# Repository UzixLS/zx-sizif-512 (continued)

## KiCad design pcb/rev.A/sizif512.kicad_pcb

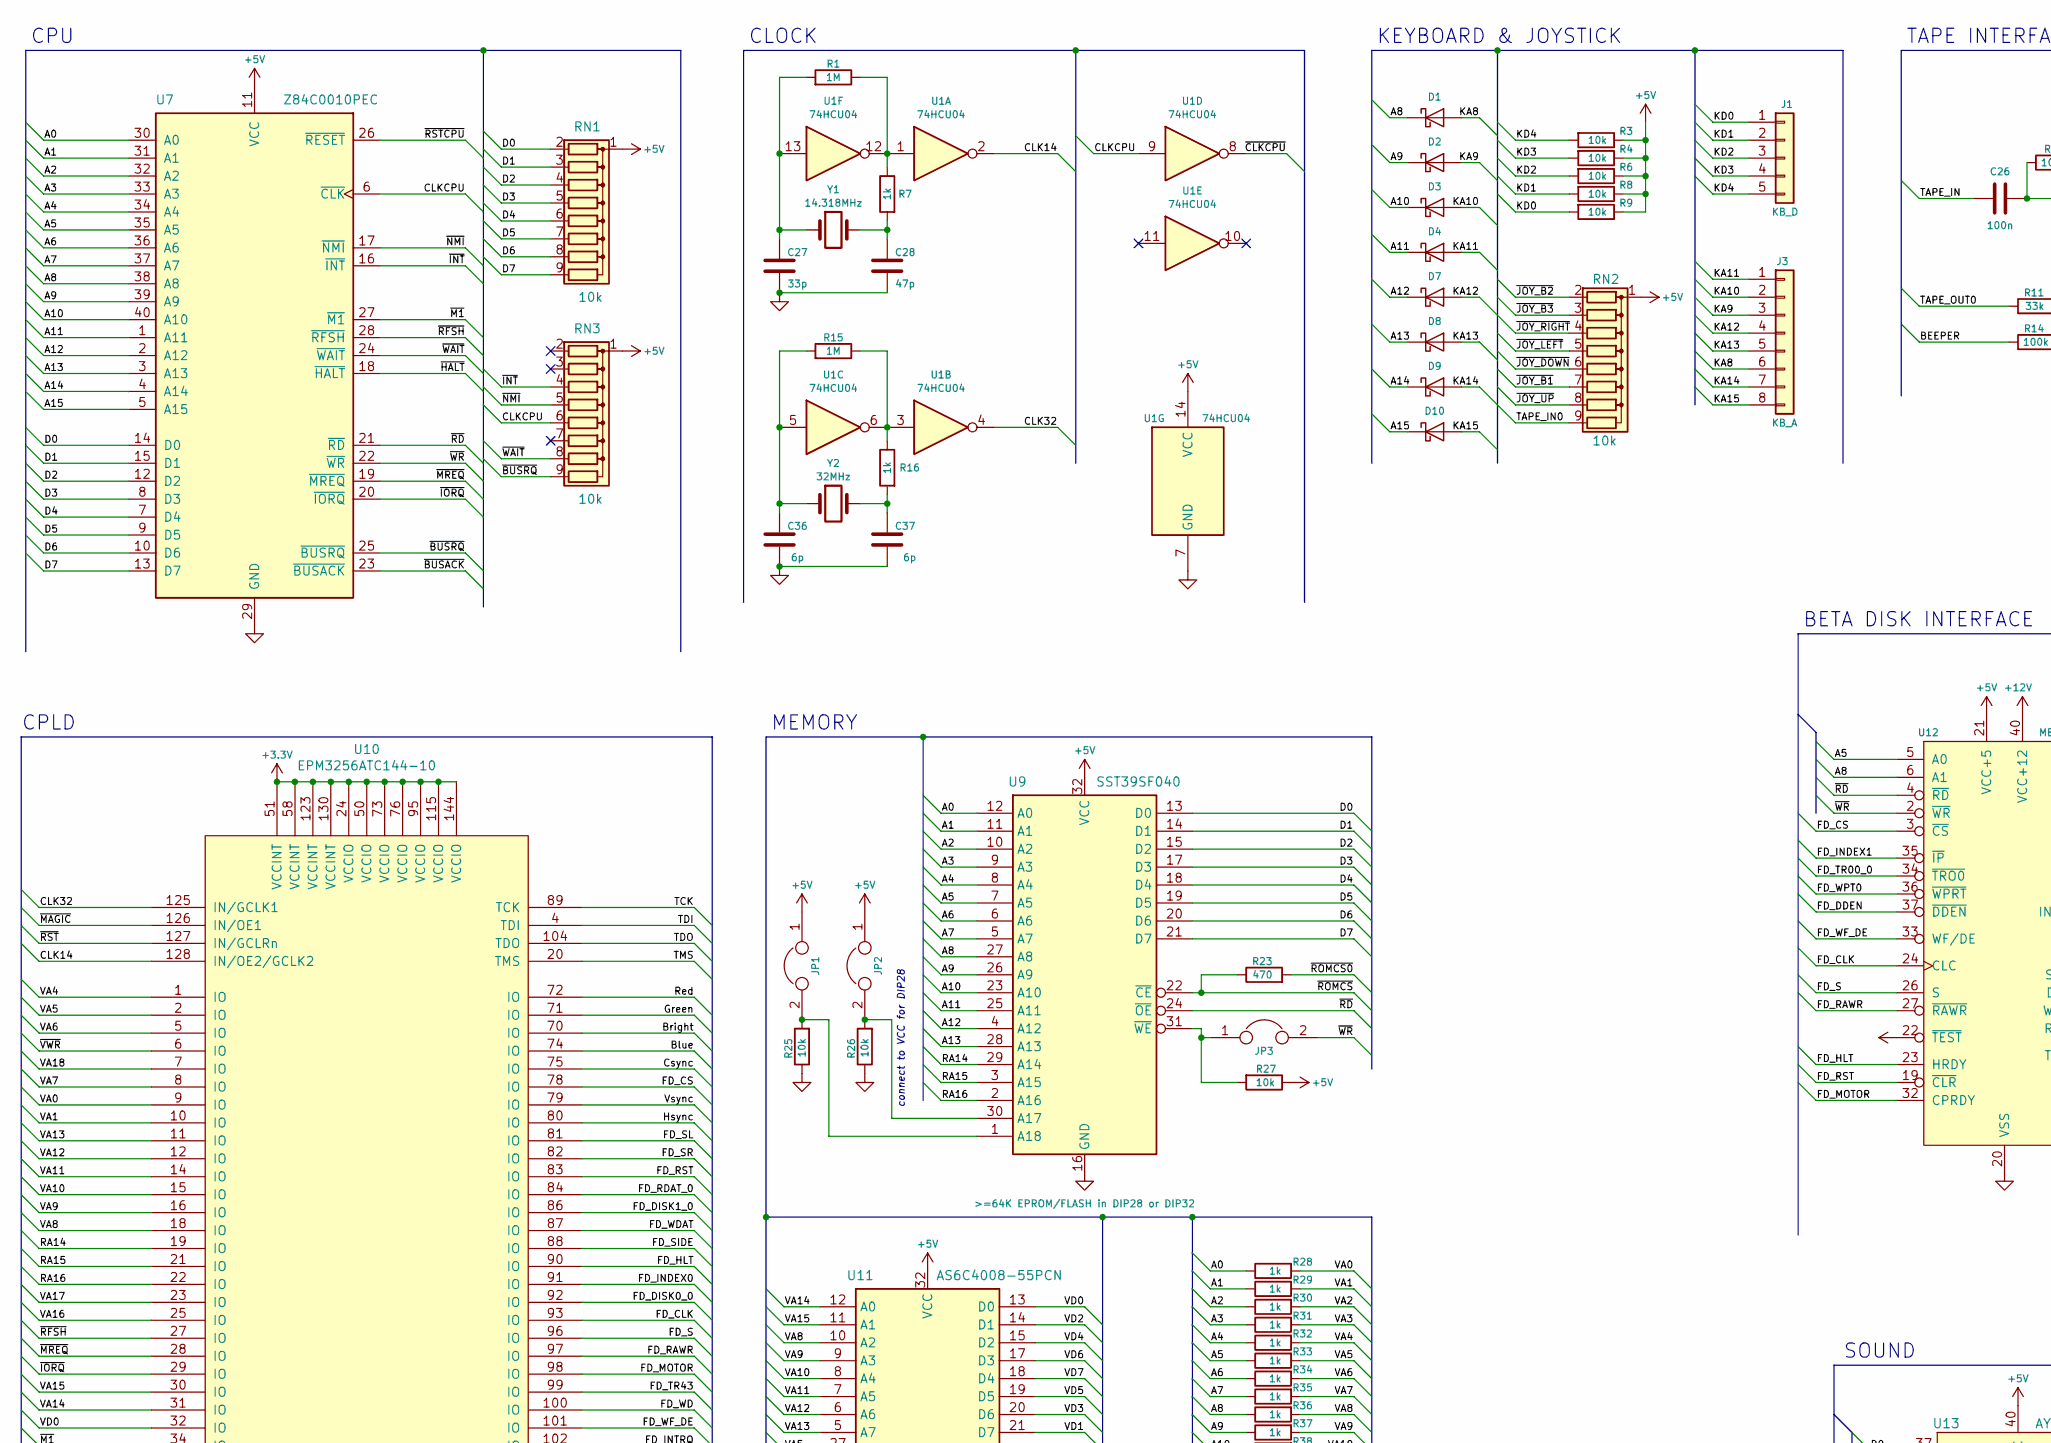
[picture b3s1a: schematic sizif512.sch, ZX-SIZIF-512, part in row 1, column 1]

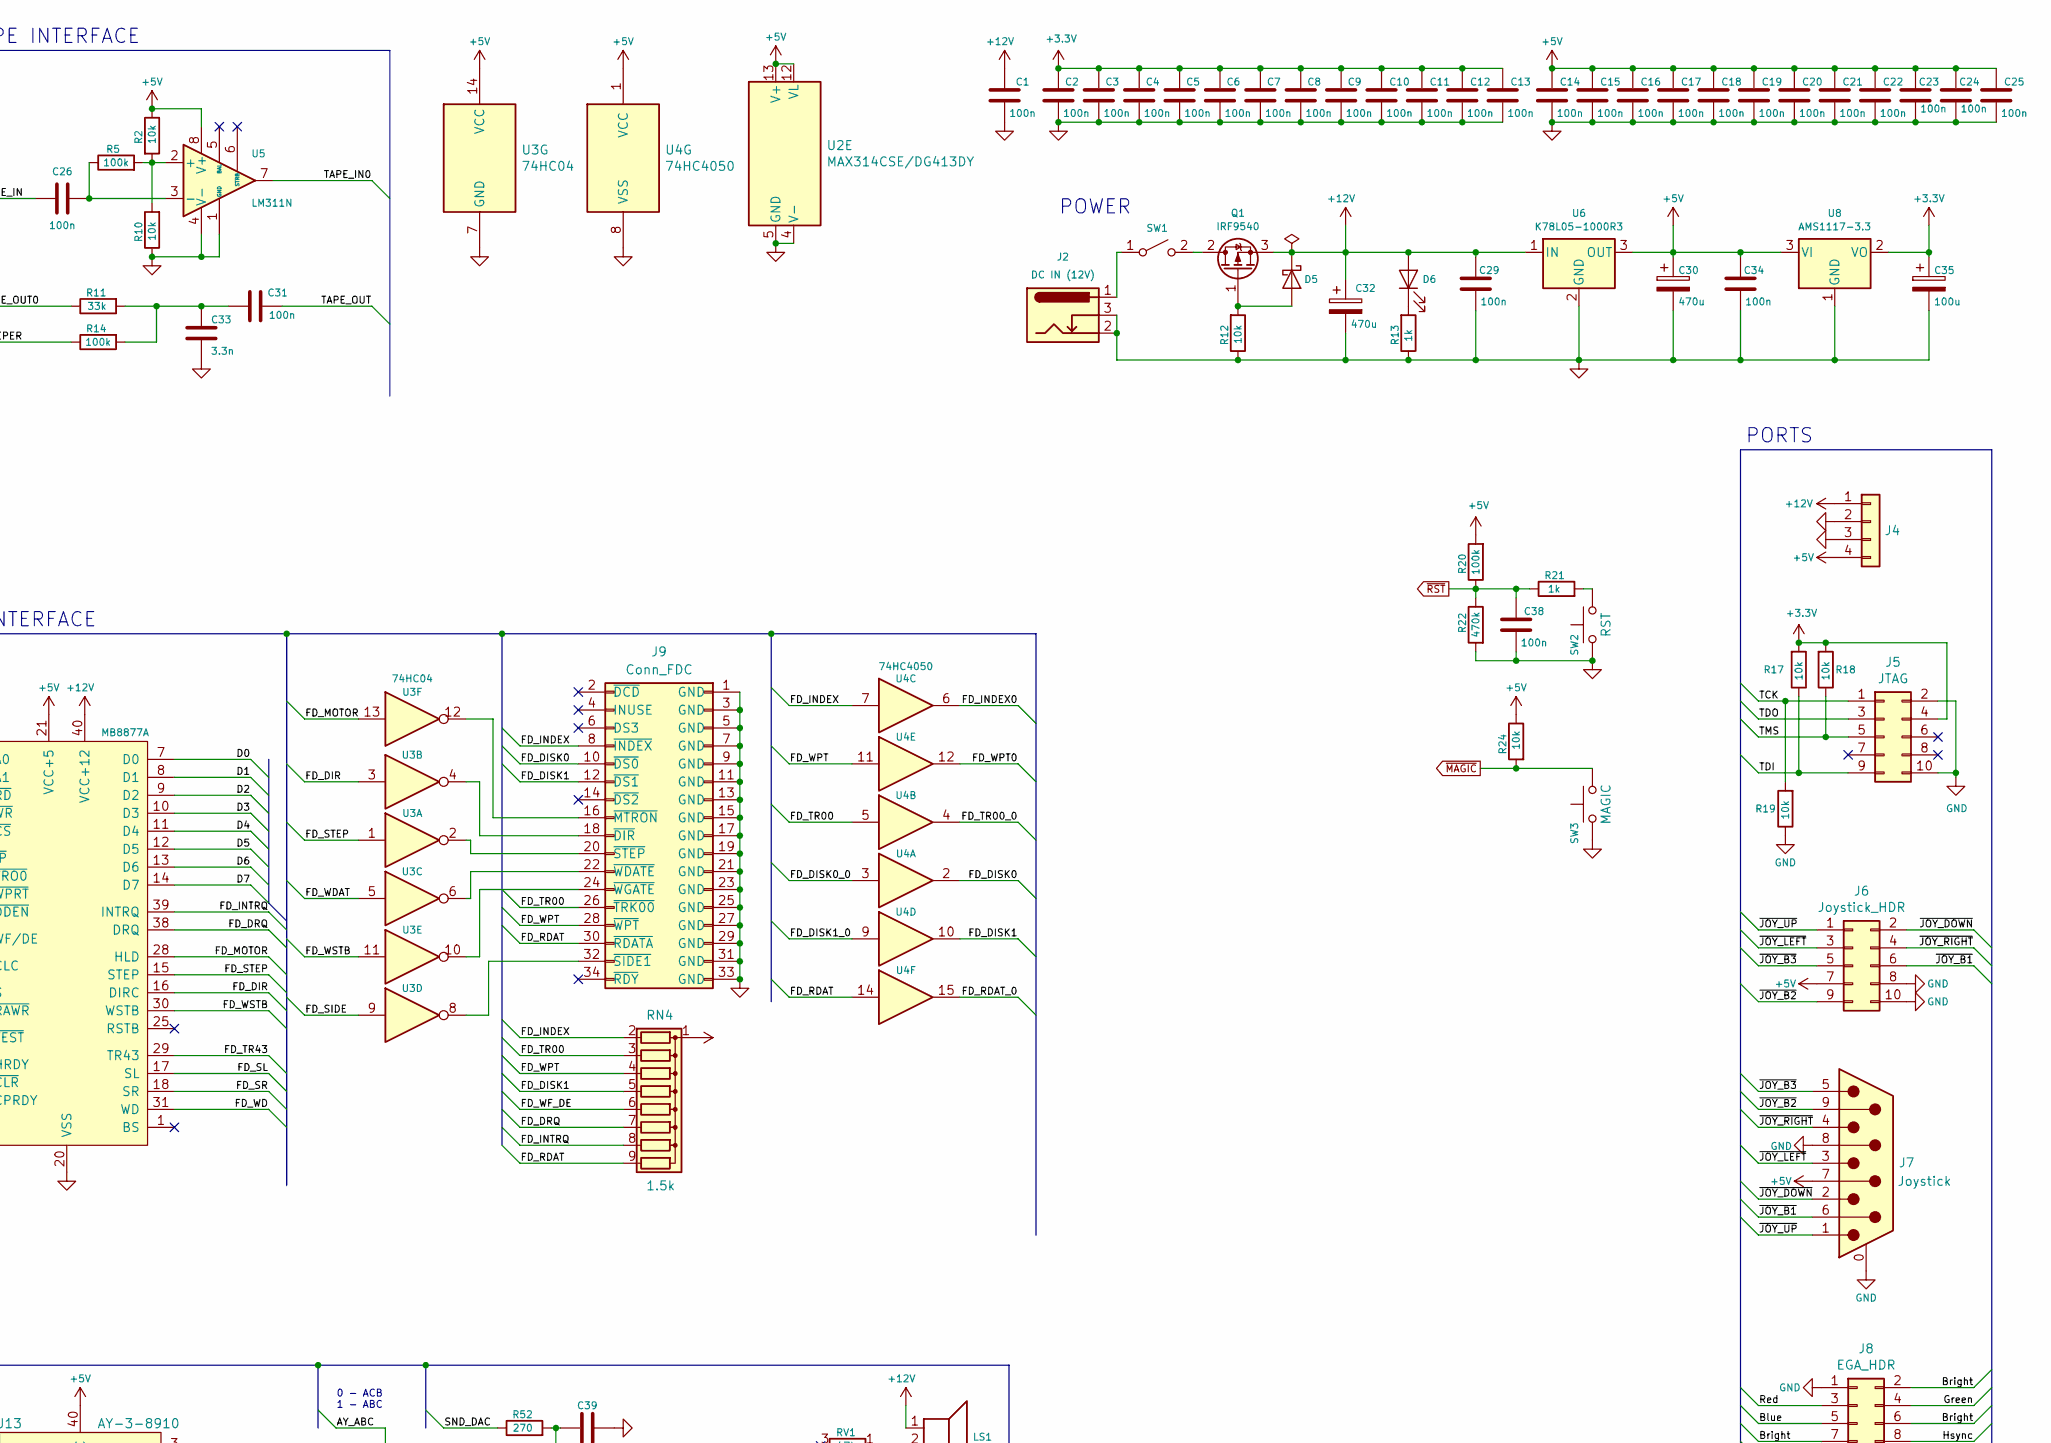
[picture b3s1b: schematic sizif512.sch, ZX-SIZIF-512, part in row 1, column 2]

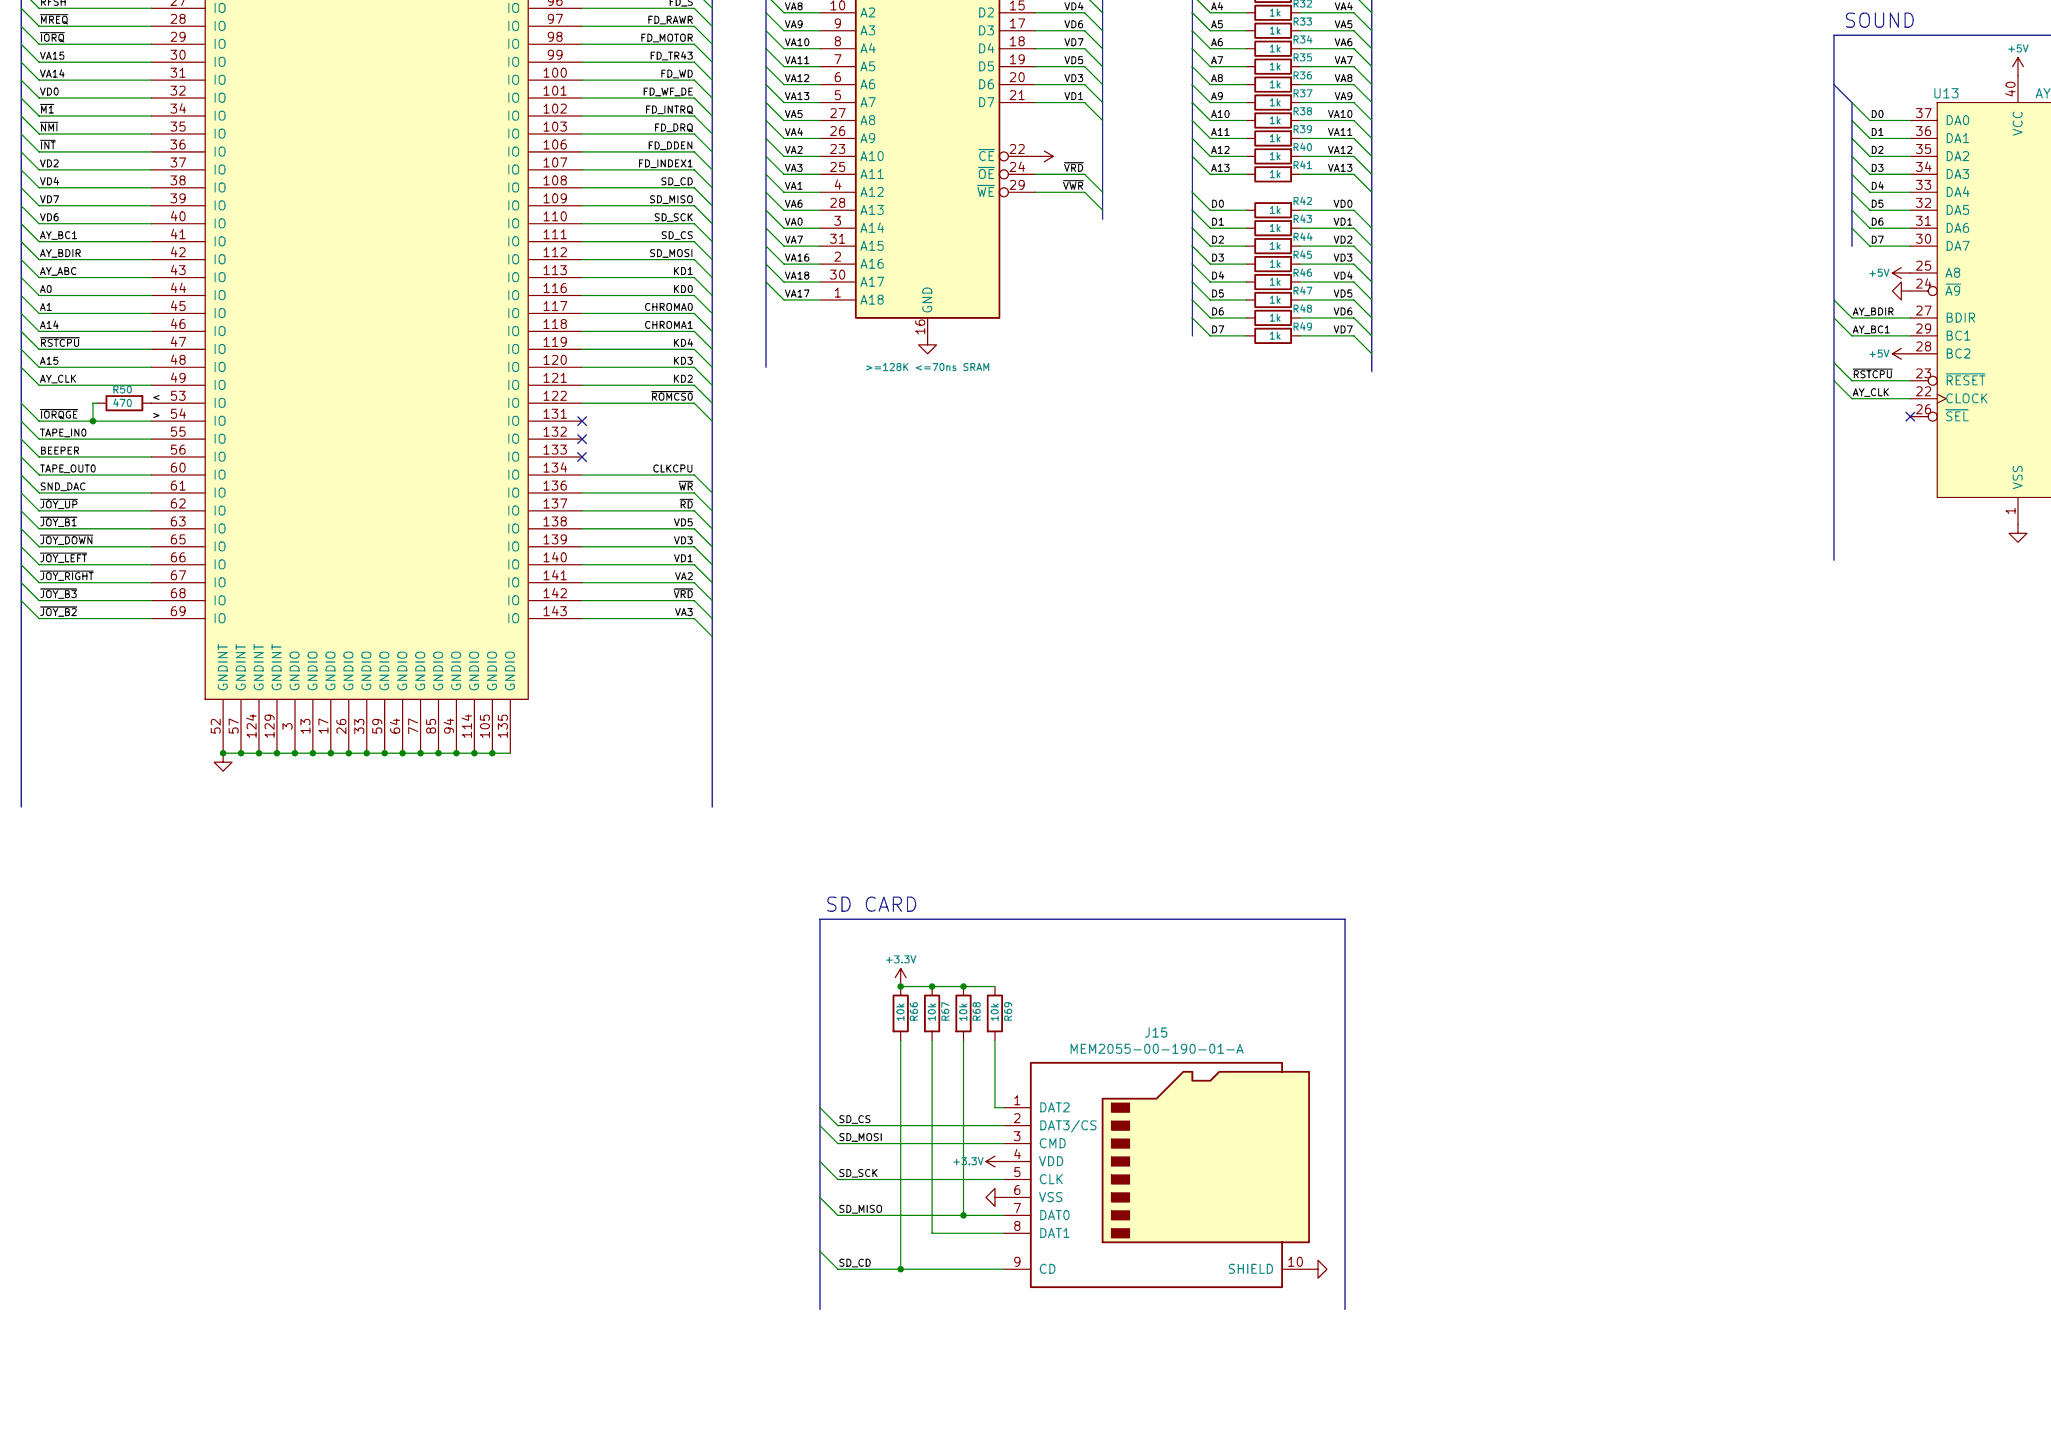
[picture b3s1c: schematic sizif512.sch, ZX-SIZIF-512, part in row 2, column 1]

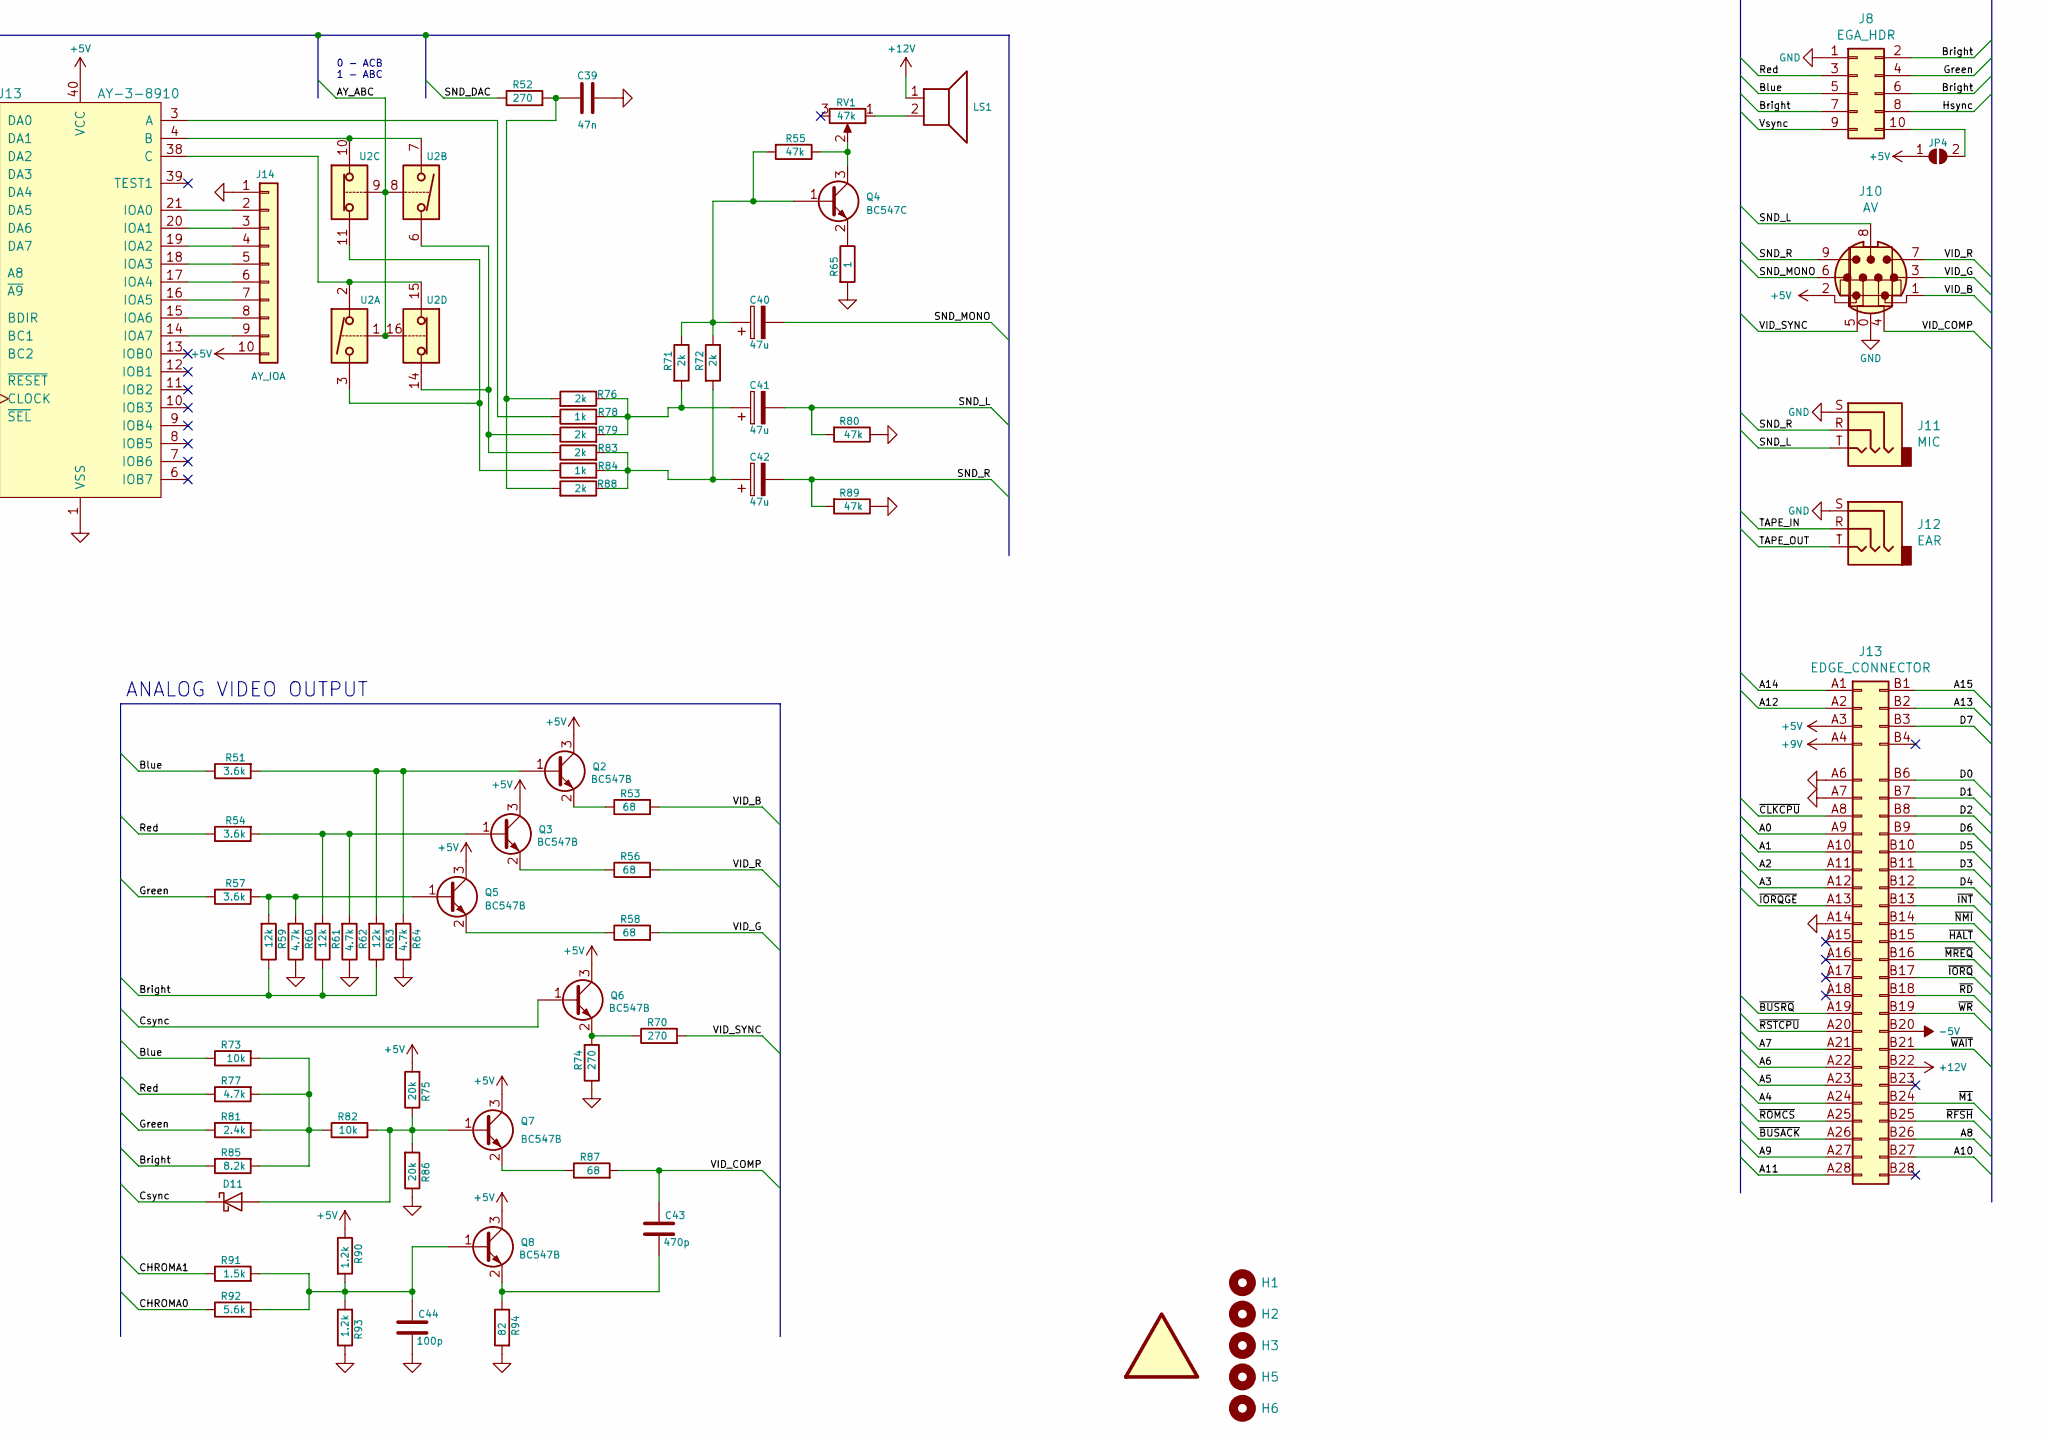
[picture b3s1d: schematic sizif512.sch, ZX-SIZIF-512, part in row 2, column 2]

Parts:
C1, C2, C14, C15, C16, C17, C18, C19, C20, C21, C22, C23, C24, C25, C26, C29, C31, C34, C38: 100n; C_Disc_D7.0mm_W2.5mm_P5.00mm
C3, C4, C5, C6, C7, C8, C9, C10, C11, C12, C13: 100n; C_0805_2012Metric_Pad1.15x1.40mm_HandSolder
C27: 33p; C_Disc_D3.8mm_W2.6mm_P2.50mm
C28: 47p; C_Disc_D3.8mm_W2.6mm_P2.50mm
C30, C32: 470u; CP_Radial_D10.0mm_P3.80mm
C33: 3.3n; C_Disc_D5.0mm_W2.5mm_P2.50mm
C35: 100u; CP_Radial_D5.0mm_P2.50mm
C36, C37: 6p; C_Disc_D3.8mm_W2.6mm_P2.50mm
C39: 47n; C_Disc_D7.0mm_W2.5mm_P5.00mm
C40, C41, C42: 47u; CP_Radial_D5.0mm_P2.50mm
C43: 470p; C_Disc_D3.8mm_W2.6mm_P2.50mm
C44: 100p; C_Disc_D3.8mm_W2.6mm_P2.50mm
D1, D2, D3, D4, D5, D7, D8, D9, D10, D11: BAT85; D_DO-35_SOD27_P2.54mm_Vertical_AnodeUp
D6: LED; LED_D4.0mm
H1, H2: MountingHole; MountingHole_5mm
H3, H5, H6: MountingHole; MountingHole_3mm
J1: DS1020-05; PinSocket_1x05_P2.54mm_Vertical
J2: DS-210; BarrelJack_Horizontal
J3: DS1020-08; PinSocket_1x08_P2.54mm_Vertical
J4: WF-4; Molex_KK-254_AE-6410-04A_1x04_P2.54mm_Vertical
J5: Conn_02x05; PinHeader_2x05_P2.54mm_Vertical
J6, J8: Conn_02x05_Odd_Even; PinHeader_2x05_P2.54mm_Vertical
J7: DB9-M; DSUB-9_Male_Horizontal_P2.77x2.84mm_EdgePinOffset4.94mm_Hou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
J9: Conn_02x17_Odd_Even; PinHeader_2x17_P2.54mm_Vertical
J10: Mini-DIN-9; minidin-9
J11, J12: PJ-313
J13: Conn_02x28_Row_Letter_First; ZX_EDGE
J14: Conn_01x10; PinHeader_1x10_P2.54mm_Vertical
J15: MEM2055-00-190-01-A; GCT-MEM2055-00-190-01-A
JP1, JP2, JP3: Jumper; PinHeader_1x02_P2.54mm_Vertical
JP4: SolderJumper_2_Open; SolderJumper-2_P1.3mm_Open_RoundedPad1.0x1.5mm
LOGO1: graphic; black-mage2
LS1: WF-2; Molex_KK-254_AE-6410-02A_1x02_P2.54mm_Vertical
Q1: IRF9540; TO-220-3_Horizontal_TabDown
Q2, Q3, Q5, Q6, Q7, Q8: BC547B; TO-92_Inline
Q4: BC547C; TO-92_Inline
R1, R15: 1M; R_Axial_DIN0204_L3.6mm_D1.6mm_P2.54mm_Vertical
R2, R3, R4, R6, R8, R9, R10, R12, R17, R18, R19, R24, R25, R26, R27, R66, R67, R68, R69, R73, R82: 10k; R_Axial_DIN0204_L3.6mm_D1.6mm_P2.54mm_Vertical
R5, R14, R20: 100k; R_Axial_DIN0204_L3.6mm_D1.6mm_P2.54mm_Vertical
R7, R13, R16, R21, R78, R84: 1k; R_Axial_DIN0204_L3.6mm_D1.6mm_P2.54mm_Vertical
R11: 33k; R_Axial_DIN0204_L3.6mm_D1.6mm_P2.54mm_Vertical
R22: 470k; R_Axial_DIN0204_L3.6mm_D1.6mm_P2.54mm_Vertical
R23, R50: 470; R_Axial_DIN0204_L3.6mm_D1.6mm_P2.54mm_Vertical
R28, R29, R30, R31, R32, R33, R34, R35, R36, R37, R38, R39, R40, R41, R42, R43, R44, R45, R46, R47, R48, R49: 1k; R_Axial_DIN0204_L3.6mm_D1.6mm_P5.08mm_Horizontal
R51, R54, R57: 3.6k; R_Axial_DIN0204_L3.6mm_D1.6mm_P2.54mm_Vertical
R52, R70, R74: 270; R_Axial_DIN0204_L3.6mm_D1.6mm_P2.54mm_Vertical
R53, R56, R58, R87: 68; R_Axial_DIN0204_L3.6mm_D1.6mm_P2.54mm_Vertical
R55, R80, R89: 47k; R_Axial_DIN0204_L3.6mm_D1.6mm_P2.54mm_Vertical
R59, R61, R63: 12k; R_Axial_DIN0204_L3.6mm_D1.6mm_P2.54mm_Vertical
R60, R62, R64, R77: 4.7k; R_Axial_DIN0204_L3.6mm_D1.6mm_P2.54mm_Vertical
R65: 1; R_Axial_DIN0204_L3.6mm_D1.6mm_P2.54mm_Vertical
R71, R72, R76, R79, R83, R88: 2k; R_Axial_DIN0204_L3.6mm_D1.6mm_P2.54mm_Vertical
R75, R86: 20k; R_Axial_DIN0204_L3.6mm_D1.6mm_P2.54mm_Vertical
R81: 2.4k; R_Axial_DIN0204_L3.6mm_D1.6mm_P2.54mm_Vertical
R85: 8.2k; R_Axial_DIN0204_L3.6mm_D1.6mm_P2.54mm_Vertical
R90, R93: 1.2k; R_Axial_DIN0204_L3.6mm_D1.6mm_P2.54mm_Vertical
R91: 1.5k; R_Axial_DIN0204_L3.6mm_D1.6mm_P2.54mm_Vertical
R92: 5.6k; R_Axial_DIN0204_L3.6mm_D1.6mm_P2.54mm_Vertical
R94: 82; R_Axial_DIN0204_L3.6mm_D1.6mm_P2.54mm_Vertical
RN1, RN2, RN3: 10k; R_Array_SIP9
RN4: 1.5k; R_Array_SIP9
RV1: 47k; Potentiometer_Runtron_RM-063_Horizontal
SW1: SW_SPST; Molex_KK-254_AE-6410-02A_1x02_P2.54mm_Vertical
SW2, SW3: WF-2; Molex_KK-254_AE-6410-02A_1x02_P2.54mm_Vertical
U1: 74HCU04; DIP-14_W7.62mm_Socket
U2: MAX314CSE/DG413DY; SOIC-16_3.9x9.9mm_P1.27mm
U3: 74HC04; SOIC-14_3.9x8.7mm_P1.27mm
U4: 74HC4050; SOIC-16_3.9x9.9mm_P1.27mm
U5: LM311N; DIP-8_W7.62mm_Socket
U6: K78L05-1000R3; TO-220-3_Horizontal_TabDown
U7: Z84C0010PEC; DIP-40_W15.24mm_Socket
U8: AMS1117-3.3; SOT-223-3_TabPin2
U9: SST39SF040; DIP-32_W15.24mm_Socket
U10: EPM3256ATC144-10; TQFP-144_20x20mm_P0.5mm
U11: AS6C4008-55PCN; DIP-32_W15.24mm_Socket
U12: MB8877A; DIP-40_W15.24mm_Socket
U13: AY-3-8910; DIP-40_W15.24mm_Socket
Y1: 14.318MHz; Crystal_HC49-U_Vertical
Y2: 32MHz; Crystal_HC49-U_Vertical

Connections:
+3V3: C2.2, C3.2, C4.2, C5.2, C6.2, C7.2, C8.2, C9.2, C10.2, C11.2, C12.2, C13.2, C35.1, J5.4, J15.4 (VDD), R17.2, R18.2, R66.1, R67.1, R68.1, R69.1, U8.2 (VO), U10.24 (VCCIO), U10.50 (VCCIO), U10.51 (VCCINT), U10.58 (VCCINT), U10.73 (VCCIO), U10.76 (VCCIO), U10.95 (VCCIO), U10.115 (VCCIO), U10.123 (VCCINT), U10.130 (VCCINT), U10.144 (VCCIO)
+5V: C14.2, C15.2, C16.2, C17.2, C18.2, C19.2, C20.2, C21.2, C22.2, C23.1, C24.1, C25.2, C30.1, C34.2, J4.4, J6.7, J7.7, J10.2, J13.A3 (Pin_a3), J14.10, JP1.1, JP2.1, JP4.1 (A), Q2.3 (C), Q3.3 (C), Q5.3 (C), Q6.3 (C), Q7.3 (C), Q8.3 (C), R2.1, R3.1, R4.1, R6.1, R8.1, R9.1, R20.2, R24.1, R27.1, R75.2, R90.1, RN1.1 (common), RN2.1 (common), RN3.1 (common), RN4.1 (common), U1.14 (VCC), U2.12 (VL), U2.13 (V+), U3.14 (VCC), U4.1 (VCC), U5.8 (V+), U6.3 (OUT), U7.11 (VCC), U8.3 (VI), U9.32 (VCC), U11.22 (~CE), U11.32 (VCC), U12.21 (VCC+5), U12.22 (~TEST), U13.25 (A8), U13.28 (BC2), U13.40 (VCC)
+12V: C1.2, C29.2, C32.1, D5.1 (K), D6.2 (A), J4.1, J13.B22 (Pin_b22), LS1.1, Q1.3 (S), U6.1 (IN), U12.40 (VCC+12)
/<: R50.2, U10.53 (IO)
/>: J13.A13 (Pin_a13), R50.1, U10.54 (IO)
/A0: J13.A9 (Pin_a9), R28.1, U7.30 (A0), U9.12 (A0), U10.44 (IO)
/A1: J13.A10 (Pin_a10), R29.1, U7.31 (A1), U9.11 (A1), U10.45 (IO)
/A2: J13.A11 (Pin_a11), R30.1, U7.32 (A2), U9.10 (A2)
/A3: J13.A12 (Pin_a12), R31.1, U7.33 (A3), U9.9 (A3)
/A4: J13.A24 (Pin_a24), R32.1, U7.34 (A4), U9.8 (A4)
/A5: J13.A23 (Pin_a23), R33.1, U7.35 (A5), U9.7 (A5), U12.5 (A0)
/A6: J13.A22 (Pin_a22), R34.1, U7.36 (A6), U9.6 (A6)
/A7: J13.A21 (Pin_a21), R35.1, U7.37 (A7), U9.5 (A7)
/A8: D1.1 (K), J13.B26 (Pin_b26), R36.1, U7.38 (A8), U9.27 (A8), U12.6 (A1)
/A9: D2.1 (K), J13.A27 (Pin_a27), R37.1, U7.39 (A9), U9.26 (A9)
/A10: D3.1 (K), J13.B27 (Pin_b27), R38.1, U7.40 (A10), U9.23 (A10)
/A11: D4.1 (K), J13.A28 (Pin_a28), R39.1, U7.1 (A11), U9.25 (A11)
/A12: D7.1 (K), J13.A2 (Pin_a2), R40.1, U7.2 (A12), U9.4 (A12)
/A13: D8.1 (K), J13.B2 (Pin_b2), R41.1, U7.3 (A13), U9.28 (A13)
/A14: D9.1 (K), J13.A1 (Pin_a1), U7.4 (A14), U10.46 (IO)
/A15: D10.1 (K), J13.B1 (Pin_b1), U7.5 (A15), U10.48 (IO)
/AY_ABC: U2.1, U2.8, U2.9, U2.16, U10.43 (IO)
/AY_BC1: U10.41 (IO), U13.29 (BC1)
/AY_BDIR: U10.42 (IO), U13.27 (BDIR)
/AY_CLK: U10.49 (IO), U13.22 (CLOCK)
/BEEPER: R14.1, U10.56 (IO)
/Blue: J8.5, R51.1, R73.1, U10.74 (IO)
/Bright: J8.2, J8.6, J8.7, R59.1, R61.1, R63.1, R85.1, U10.70 (IO)
/CHROMA0: R92.1, U10.117 (IO)
/CHROMA1: R91.1, U10.118 (IO)
/CLK14: U1.2, U10.128 (IN/OE2/GCLK2)
/CLK32: U1.4, U10.125 (IN/GCLK1)
/CLKCPU: RN3.6 (R5), U1.9, U7.6 (~CLK~), U10.134 (IO)
/Csync: D11.1 (K), Q6.1 (B), U10.75 (IO)
/D0: J13.B6 (Pin_b6), R42.1, RN1.2 (R1), U7.14 (D0), U9.13 (D0), U12.7 (D0), U13.37 (DA0)
/D1: J13.B7 (Pin_b7), R43.1, RN1.3 (R2), U7.15 (D1), U9.14 (D1), U12.8 (D1), U13.36 (DA1)
/D2: J13.B8 (Pin_b8), R44.1, RN1.4 (R3), U7.12 (D2), U9.15 (D2), U12.9 (D2), U13.35 (DA2)
/D3: J13.B11 (Pin_b11), R45.1, RN1.5 (R4), U7.8 (D3), U9.17 (D3), U12.10 (D3), U13.34 (DA3)
/D4: J13.B12 (Pin_b12), R46.1, RN1.6 (R5), U7.7 (D4), U9.18 (D4), U12.11 (D4), U13.33 (DA4)
/D5: J13.B10 (Pin_b10), R47.1, RN1.7 (R6), U7.9 (D5), U9.19 (D5), U12.12 (D5), U13.32 (DA5)
/D6: J13.B9 (Pin_b9), R48.1, RN1.8 (R7), U7.10 (D6), U9.20 (D6), U12.13 (D6), U13.31 (DA6)
/D7: J13.B3 (Pin_b3), R49.1, RN1.9 (R8), U7.13 (D7), U9.21 (D7), U12.14 (D7), U13.30 (DA7)
/FD_CLK: U10.93 (IO), U12.24 (CLC)
/FD_CS: U10.78 (IO), U12.3 (~CS)
/FD_DDEN: U10.106 (IO), U12.37 (~DDEN)
/FD_DIR: U3.3, U12.16 (DIRC)
/FD_DISK0: J9.10 (~DS0), U4.2
/FD_DISK0_0: U4.3, U10.92 (IO)
/FD_DISK1: J9.12 (~DS1), RN4.5 (R4), U4.10
/FD_DISK1_0: U4.9, U10.86 (IO)
/FD_DRQ: RN4.7 (R6), U10.103 (IO), U12.38 (DRQ)
/FD_HLT: U10.90 (IO), U12.23 (HRDY)
/FD_INDEX: J9.8 (~INDEX), RN4.2 (R1), U4.7
/FD_INDEX0: U4.6, U10.91 (IO)
/FD_INDEX1: U10.107 (IO), U12.35 (~IP)
/FD_INTRQ: RN4.8 (R7), U10.102 (IO), U12.39 (INTRQ)
/FD_MOTOR: U3.13, U10.98 (IO), U12.28 (HLD), U12.32 (CPRDY)
/FD_RAWR: U10.97 (IO), U12.27 (~RAWR)
/FD_RDAT: J9.30 (~RDATA), RN4.9 (R8), U4.14
/FD_RDAT_0: U4.15, U10.84 (IO)
/FD_RST: U10.83 (IO), U12.19 (~CLR)
/FD_S: U10.96 (IO), U12.26 (S)
/FD_SIDE: U3.9, U10.88 (IO)
/FD_SL: U10.81 (IO), U12.17 (SL)
/FD_SR: U10.82 (IO), U12.18 (SR)
/FD_STEP: U3.1, U12.15 (STEP)
/FD_TR00: J9.26 (~TRK00), RN4.3 (R2), U4.5
/FD_TR00_0: U4.4, U12.34 (~TRO0)
/FD_TR43: U10.99 (IO), U12.29 (TR43)
/FD_WD: U10.100 (IO), U12.31 (WD)
/FD_WDAT: U3.5, U10.87 (IO)
/FD_WF_DE: RN4.6 (R5), U10.101 (IO), U12.33 (WF/DE)
/FD_WPT: J9.28 (~WPT), RN4.4 (R3), U4.11
/FD_WPT0: U4.12, U12.36 (~WPRT)
/FD_WSTB: U3.11, U12.30 (WSTB)
/Green: J8.4, R57.1, R81.1, U10.71 (IO)
/Hsync: J8.8, U10.80 (IO)
/KA8: D1.2 (A), J3.6
/KA9: D2.2 (A), J3.3
/KA10: D3.2 (A), J3.2
/KA11: D4.2 (A), J3.1
/KA12: D7.2 (A), J3.4
/KA13: D8.2 (A), J3.5
/KA14: D9.2 (A), J3.7
/KA15: D10.2 (A), J3.8
/KD0: J1.1, R9.2, U10.116 (IO)
/KD1: J1.2, R8.2, U10.113 (IO)
/KD2: J1.3, R6.2, U10.121 (IO)
/KD3: J1.4, R4.2, U10.120 (IO)
/KD4: J1.5, R3.2, U10.119 (IO)
/RA14: U9.29 (A14), U10.19 (IO)
/RA15: U9.3 (A15), U10.21 (IO)
/RA16: U9.2 (A16), U10.22 (IO)
/Red: J8.3, R54.1, R77.1, U10.72 (IO)
/SD_CD: J15.9 (CD), R66.2, U10.108 (IO)
/SD_CS: J15.2 (DAT3/CS), U10.111 (IO)
/SD_MISO: J15.7 (DAT0), R68.2, U10.109 (IO)
/SD_MOSI: J15.3 (CMD), U10.112 (IO)
/SD_SCK: J15.5 (CLK), U10.110 (IO)
/SND_DAC: R52.1, U10.61 (IO)
/SND_L: C41.2, J10.8, J11.T, R80.2
/SND_MONO: C40.2, J10.6
/SND_R: C42.2, J10.9, J11.R, R89.2
/TAPE_IN: C26.2, J12.R
/TAPE_IN0: RN2.9 (R8), U5.7, U10.55 (IO)
/TAPE_OUT: C31.1, J12.T
/TAPE_OUT0: R11.1, U10.60 (IO)
/TCK: J5.1, R19.2, U10.89 (TCK)
/TDI: J5.9, R17.1, U10.4 (TDI)
/TDO: J5.3, U10.104 (TDO)
/TMS: J5.5, R18.1, U10.20 (TMS)
/VA0: R28.2, U10.9 (IO), U11.3 (A14)
/VA1: R29.2, U10.10 (IO), U11.4 (A12)
/VA2: R30.2, U10.141 (IO), U11.23 (A10)
/VA3: R31.2, U10.143 (IO), U11.25 (A11)
/VA4: R32.2, U10.1 (IO), U11.26 (A9)
/VA5: R33.2, U10.2 (IO), U11.27 (A8)
/VA6: R34.2, U10.5 (IO), U11.28 (A13)
/VA7: R35.2, U10.8 (IO), U11.31 (A15)
/VA8: R36.2, U10.18 (IO), U11.10 (A2)
/VA9: R37.2, U10.16 (IO), U11.9 (A3)
/VA10: R38.2, U10.15 (IO), U11.8 (A4)
/VA11: R39.2, U10.14 (IO), U11.7 (A5)
/VA12: R40.2, U10.12 (IO), U11.6 (A6)
/VA13: R41.2, U10.11 (IO), U11.5 (A7)
/VA14: U10.31 (IO), U11.12 (A0)
/VA15: U10.30 (IO), U11.11 (A1)
/VA16: U10.25 (IO), U11.2 (A16)
/VA17: U10.23 (IO), U11.1 (A18)
/VA18: U10.7 (IO), U11.30 (A17)
/VD0: R42.2, U10.32 (IO), U11.13 (D0)
/VD1: R43.2, U10.140 (IO), U11.21 (D7)
/VD2: R44.2, U10.37 (IO), U11.14 (D1)
/VD3: R45.2, U10.139 (IO), U11.20 (D6)
/VD4: R46.2, U10.38 (IO), U11.15 (D2)
/VD5: R47.2, U10.138 (IO), U11.19 (D5)
/VD6: R48.2, U10.40 (IO), U11.17 (D3)
/VD7: R49.2, U10.39 (IO), U11.18 (D4)
/VID_B: J10.1, R53.2
/VID_COMP: C43.1, J10.4, R87.2
/VID_G: J10.3, R58.2
/VID_R: J10.7, R56.2
/VID_SYNC: J10.5, R70.2
/Vsync: J8.9, U10.79 (IO)
/~BUSACK: J13.A26 (Pin_a26), U7.23 (~BUSACK~)
/~BUSRQ: J13.A19 (Pin_a19), RN3.9 (R8), U7.25 (~BUSRQ~)
/~CLKCPU: J13.A8 (Pin_a8), U1.8
/~HALT: J13.B15 (Pin_b15), U7.18 (~HALT~)
/~INT: J13.B13 (Pin_b13), RN3.4 (R3), U7.16 (~INT~), U10.36 (IO)
/~IORQ: J13.B17 (Pin_b17), U7.20 (~IORQ~), U10.29 (IO)
/~JOY_B1: J6.6, J7.6, RN2.7 (R6), U10.63 (IO)
/~JOY_B2: J6.9, J7.9, RN2.2 (R1), U10.69 (IO)
/~JOY_B3: J6.5, J7.5, RN2.3 (R2), U10.68 (IO)
/~JOY_DOWN: J6.2, J7.2, RN2.6 (R5), U10.65 (IO)
/~JOY_LEFT: J6.3, J7.3, RN2.5 (R4), U10.66 (IO)
/~JOY_RIGHT: J6.4, J7.4, RN2.4 (R3), U10.67 (IO)
/~JOY_UP: J6.1, J7.1, RN2.8 (R7), U10.62 (IO)
/~M1: J13.B24 (Pin_b24), U7.27 (~M1~), U10.34 (IO)
/~MREQ: J13.B16 (Pin_b16), U7.19 (~MREQ~), U10.28 (IO)
/~NMI: J13.B14 (Pin_b14), RN3.5 (R4), U7.17 (~NMI~), U10.35 (IO)
/~RD: J13.B18 (Pin_b18), U7.21 (~RD~), U9.24 (~OE), U10.137 (IO), U12.4 (~RD)
/~RFSH: J13.B25 (Pin_b25), U7.28 (~RFSH~), U10.27 (IO)
/~ROMCS: J13.A25 (Pin_a25), R23.1, U9.22 (~CE)
/~ROMCS0: R23.2, U10.122 (IO)
/~RSTCPU: J13.A20 (Pin_a20), U7.26 (~RESET~), U10.47 (IO), U13.23 (~RESET~)
/~VRD: U10.142 (IO), U11.24 (~OE)
/~VWR: U10.6 (IO), U11.29 (~WE)
/~WAIT: J13.B21 (Pin_b21), RN3.8 (R7), U7.24 (~WAIT~)
/~WR: J13.B19 (Pin_b19), JP3.2, U7.22 (~WR~), U10.136 (IO), U12.2 (~WR)
GND: C1.1, C2.1, C3.1, C4.1, C5.1, C6.1, C7.1, C8.1, C9.1, C10.1, C11.1, C12.1, C13.1, C14.1, C15.1, C16.1, C17.1, C18.1, C19.1, C20.1, C21.1, C22.1, C23.2, C24.2, C25.1, C27.1, C28.1, C29.1, C30.2, C32.2, C33.1, C34.1, C35.2, C36.1, C37.1, C38.1, C39.1, C44.2, J2.2, J2.3, J4.2, J4.3, J5.2, J5.10, J6.8, J6.10, J7.0 (PAD), J7.8, J8.1, J9.1 (GND), J9.3 (GND), J9.5 (GND), J9.7 (GND), J9.9 (GND), J9.11 (GND), J9.13 (GND), J9.15 (GND), J9.17 (GND), J9.19 (GND), J9.21 (GND), J9.23 (GND), J9.25 (GND), J9.27 (GND), J9.29 (GND), J9.31 (GND), J9.33 (GND), J10.0, J11.S, J12.S, J13.A6 (Pin_a6), J13.A7 (Pin_a7), J13.A14 (Pin_a14), J14.1, J15.6 (VSS), J15.10 (SHIELD), R10.1, R12.1, R13.1, R19.1, R22.2, R25.1, R26.1, R60.1, R62.1, R64.1, R65.2, R74.1, R80.1, R86.1, R89.1, R93.1, R94.2, SW2.1, SW3.1, U1.7 (GND), U2.4 (V-), U2.5 (GND), U3.7 (GND), U4.8 (VSS), U5.1 (GND), U5.4 (V-), U6.2 (GND), U7.29 (GND), U8.1 (GND), U9.16 (GND), U10.3 (GNDIO), U10.13 (GNDIO), U10.17 (GNDIO), U10.26 (GNDIO), U10.33 (GNDIO), U10.52 (GNDINT), U10.57 (GNDINT), U10.59 (GNDIO), U10.64 (GNDIO), U10.77 (GNDIO), U10.85 (GNDIO), U10.94 (GNDIO), U10.105 (GNDIO), U10.114 (GNDIO), U10.124 (GNDINT), U10.129 (GNDINT), U10.135 (GNDIO), U11.16 (GND), U12.20 (VSS), U13.1 (VSS), U13.24 (~A9~)
unnamed: C26.1, R5.1, U5.3 (-)
unnamed: C27.2, R1.2, U1.13, Y1.1
unnamed: C28.2, R7.2, Y1.2
unnamed: C31.2, C33.2, R11.2, R14.2
unnamed: C36.2, R15.2, U1.5, Y2.1
unnamed: C37.2, R16.2, Y2.2
unnamed: C39.2, R52.2, R76.2, R88.2
unnamed: C40.1, Q4.1 (B), R55.2, R71.1, R72.1
unnamed: C41.1, R71.2, R76.1, R78.2, R79.2
unnamed: C42.1, R72.2, R83.2, R84.2, R88.1
unnamed: C43.2, Q8.2 (E), R94.1
unnamed: C44.1, Q8.1 (B), R90.2, R91.2, R92.2, R93.2
unnamed: D5.2 (A), Q1.1 (G), R12.2
unnamed: D6.1 (K), R13.2
unnamed: D11.2 (A), Q7.1 (B), R75.1, R82.2, R86.2
unnamed: J2.1, SW1.1 (A)
unnamed: J8.10, JP4.2 (B)
unnamed: J9.16 (~MTRON), U3.12
unnamed: J9.18 (~DIR), U3.4
unnamed: J9.20 (~STEP), U3.2
unnamed: J9.22 (~WDATE), U3.6
unnamed: J9.24 (~WGATE), U3.10
unnamed: J9.32 (~SIDE1), U3.8
unnamed: J14.2, U13.21 (IOA0)
unnamed: J14.3, U13.20 (IOA1)
unnamed: J14.4, U13.19 (IOA2)
unnamed: J14.5, U13.18 (IOA3)
unnamed: J14.6, U13.17 (IOA4)
unnamed: J14.7, U13.16 (IOA5)
unnamed: J14.8, U13.15 (IOA6)
unnamed: J14.9, U13.14 (IOA7)
unnamed: J15.1 (DAT2), R69.2
unnamed: J15.8 (DAT1), R67.2
unnamed: JP1.2, R25.2, U9.1 (A18)
unnamed: JP2.2, R26.2, U9.30 (A17)
unnamed: JP3.1, R27.2, U9.31 (~WE)
unnamed: LS1.2, RV1.1
unnamed: Q1.2 (D), SW1.2 (B)
unnamed: Q2.1 (B), R51.2, R63.2, R64.2
unnamed: Q2.2 (E), R53.1
unnamed: Q3.1 (B), R54.2, R61.2, R62.2
unnamed: Q3.2 (E), R56.1
unnamed: Q4.2 (E), R65.1
unnamed: Q4.3 (C), R55.1, RV1.2
unnamed: Q5.1 (B), R57.2, R59.2, R60.2
unnamed: Q5.2 (E), R58.1
unnamed: Q6.2 (E), R70.1, R74.2
unnamed: Q7.2 (E), R87.1
unnamed: R1.1, R7.1, U1.1, U1.12
unnamed: R2.2, R5.2, R10.2, U5.2 (+)
unnamed: R15.1, R16.1, U1.3, U1.6
unnamed: R21.2, SW2.2
unnamed: R73.2, R77.2, R81.2, R82.1, R85.2
unnamed: R78.1, U13.3 (A)
unnamed: R79.1, R83.1, U2.6, U2.14
unnamed: R84.1, U2.3, U2.11
unnamed: U2.7, U2.10, U13.4 (B)
unnamed: U2.2, U2.15, U13.38 (C)
~MAGIC: R24.2, SW3.2, U10.126 (IN/OE1)
~RST: C38.2, R20.1, R21.1, R22.1, U10.127 (IN/GCLRn)

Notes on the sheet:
SOUND
CLOCK
CPU
POWER
connect to VCC for DIP28
MEMORY
CPLD
BETA DISK INTERFACE
ANALOG VIDEO OUTPUT
KEYBOARD & JOYSTICK
TAPE INTERFACE
SD CARD
0 - ACB 1 - ABC
PORTS

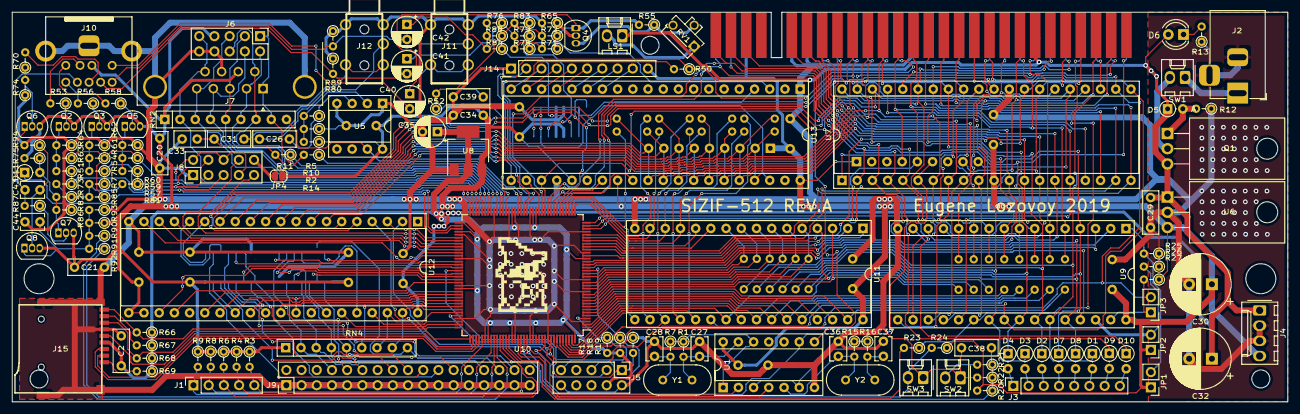
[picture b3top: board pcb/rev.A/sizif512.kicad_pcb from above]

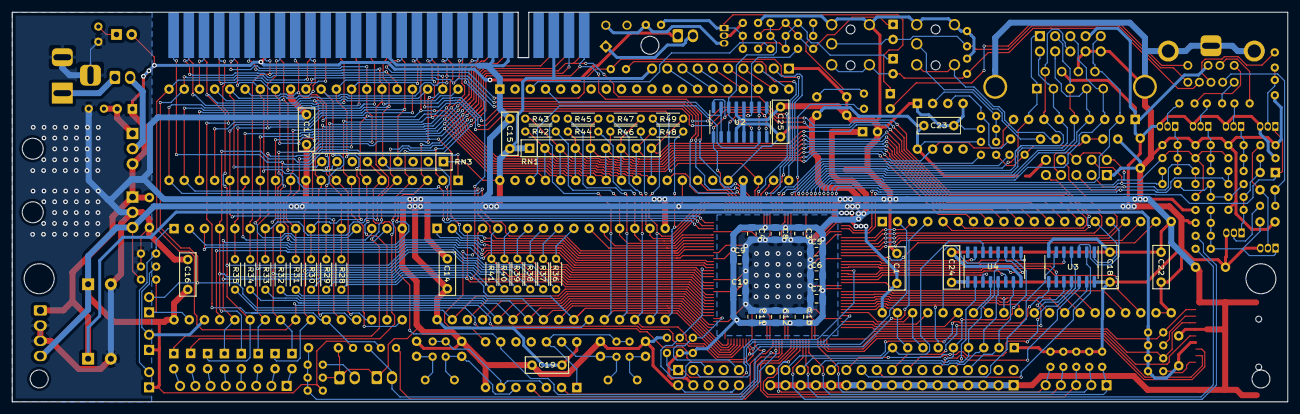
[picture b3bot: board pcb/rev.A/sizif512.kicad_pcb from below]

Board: 2 copper layers, 213.0 x 65.1 mm, 206 parts (49 on the bottom side), 230 nets.
